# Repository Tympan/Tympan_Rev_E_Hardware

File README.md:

# Tympan Rev E Hardware Light
Repository for Tympan Rev E Light Electronics and case designs. This version of the Rev E is based on the Teensy 4.1 by PJRC and incorporates the Teensy 4.1 into our own design, as we did with the Tympan Rev D. This version is light in that it does not contain an on-board AIC, and is meant to be a PCB bridge between the Teensy 4.1 and the AIC Shield.

This is a work in progress.

## Check Back For Updates

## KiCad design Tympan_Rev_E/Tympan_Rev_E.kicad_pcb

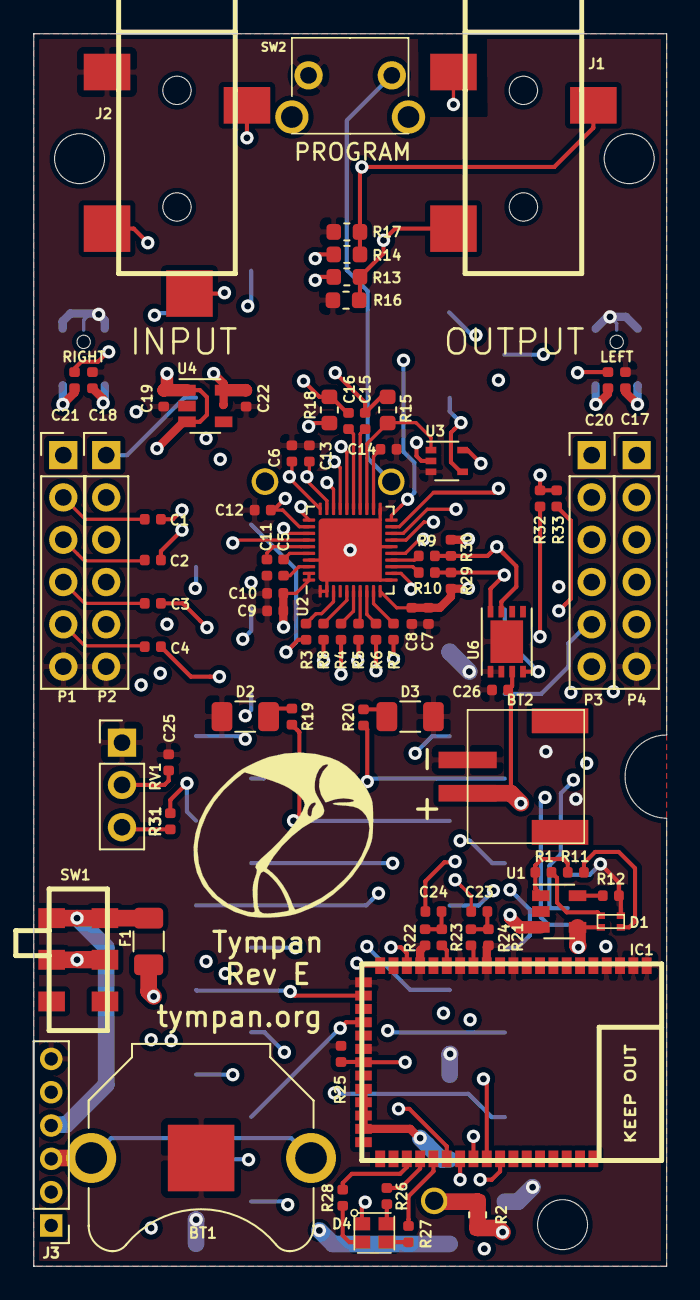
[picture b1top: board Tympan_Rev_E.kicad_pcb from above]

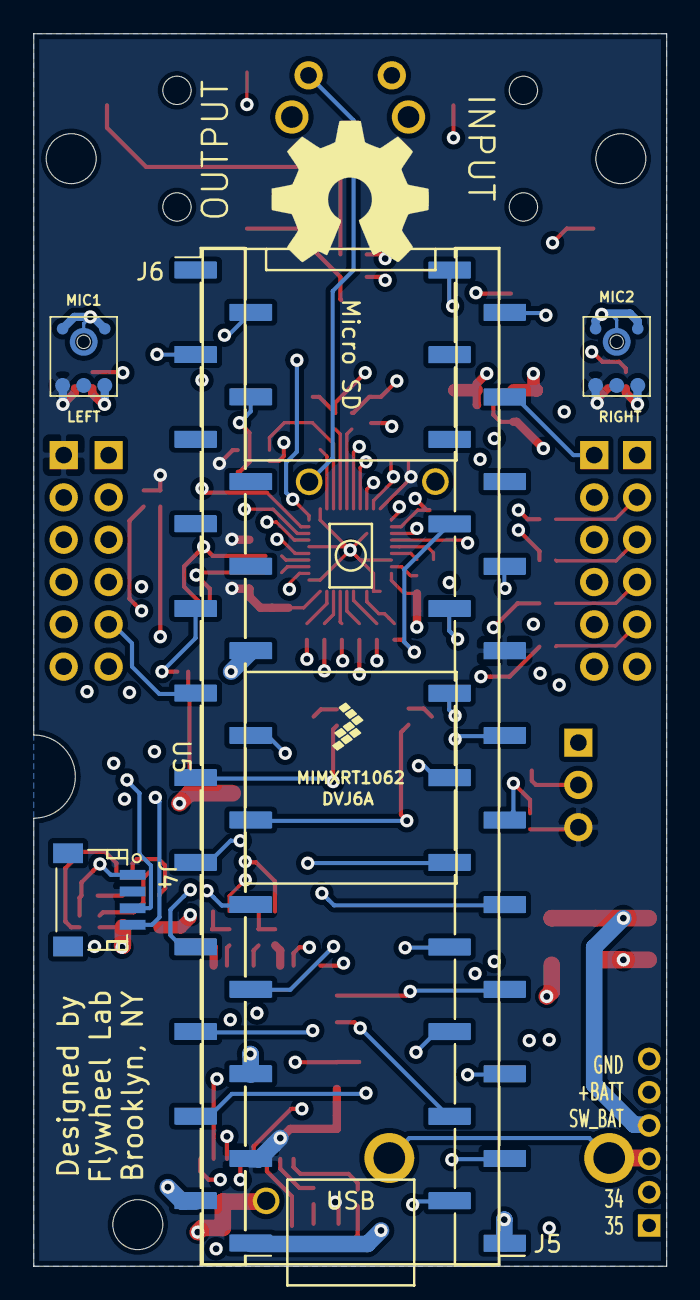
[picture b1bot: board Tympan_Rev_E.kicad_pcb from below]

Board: 4 copper layers, 38.0 x 74.0 mm, 91 parts (6 on the bottom side), 95 nets.

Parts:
BT1: Battery_Cell; BatteryHolder_Keystone_3001_1x12mm
BT2: 4UCON-20519; 4UCON-0217-20519
C1, C2, C3, C4, C5, C11, C15, C16, C23, C24: 2.2uF; C_0402_1005Metric
C6, C8, C10, C13, C17, C18, C25: 0.1uF; C_0402_1005Metric
C7, C9, C14: 10uF; C_0402_1005Metric
C12, C19, C20, C21, C22, C26: 1uF; C_0402_1005Metric
D1: APHB1608SGNC; ABHB1608S
D2, D3: LED; C_1206_3216Metric
D4: Led_RGB_CA; CLMVB-FKA-CFHEHLCBB7a363
F1: FUSE; C_1206_3216Metric
IC1: BC127
J1: SJ-3523-SMT-TR
J2: SJ-3524-SMT-TR-PI; SJ-3524-SMT-TR
J3: Conn_01x06; Pin_Header_Straight_1x06_Pitch2.00mm
J4: Qwiik Connector; JST_SH_SM04B-SRSS-TB_04x1.00mm_Angled
J5, J6: Conn_01x24; Pin_Header_Straight_1x24_Pitch2.54mm_SMD_Pin1Left
MIC1, MIC2: SPM0687LR5H-1
P1, P2, P3, P4: CONN_01X06; PinHeader_1x06_P2.54mm_Vertical
P6, P7, P8: CONN_01X01; MountingHole_3mm
R1, R11, R21, R22: 1K; R_0402_1005Metric
R2, R16, R17: DNP; R_0603_1608Metric
R3, R4, R5, R6, R7, R8, R9, R10: 33R; R_0402_1005Metric
R12: 2.2K; R_0402_1005Metric
R13, R14: 0R; R_0603_1608Metric
R15, R18: 2.2K; R_0603_1608Metric
R19, R20: 240R; R_0402_1005Metric
R23, R24, R31: 10K; R_0402_1005Metric
R25: 100K; R_0402_1005Metric
R26, R27, R28: 470R; R_0402_1005Metric
R29, R30, R32, R33: 4K7; R_0402_1005Metric
RV1: POT; PinHeader_1x03_P2.54mm_Vertical
SW1: CL-SB-22A
SW2: SW_Push; MJTP1117
U1: MCP73831; SOT-23-5
U2: TLV320AIC3206IRSBT; UQFN-40-1EP_5x5mm_P0.4mm_EP3.8x3.8mm
U3: 74LVC1G66; SOT-353_SC-70-5
U4: LP5907MFX-1.8; SOT-23-5
U5: Teensy4.1; Teensy41_SMT
U6: LC709203; WDFN8_3X4mm_0.65P

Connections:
+1V8: C9.1, C10.1, C12.1, C13.1, C22.1, P1.1, U2.29, U2.32, U2.39, U2.40, U4.5
+3V3: C6.2, C7.2, C8.2, C17.2, C18.2, D4.1, IC1.30, IC1.31, IC1.32, IC1.33, J4.2, J5.15, J6.22, MIC1.4, MIC2.4, P4.1, R29.1, R30.1, R31.2, R32.2, R33.2, RV1.3, U2.10, U2.30, U3.5, U5.15, U5.46
+BATT: BT2.1, C26.1, J3.5, SW1.2, SW1.5, U1.3, U6.3
/34_RX8: J3.2, U5.26
/35_TX8: J3.1, U5.27
/ALARMB: U5.33, U6.4
/BCLK: P2.3, R4.1, U5.43
/BT_CTS: IC1.40, U5.5
/BT_PIO0: IC1.23, U5.7
/BT_PIO5: IC1.25, U5.4
/BT_RTS: IC1.43, U5.6
/BT_RX: IC1.42, U5.3
/BT_TX: IC1.41, U5.2
/BT_nRESET: IC1.44, R31.1, U5.11
/DIN: R6.1, U5.9
/DIN_1: P4.3, U5.24
/DOUT: R7.1, U5.10
/DOUT_1: P4.2, U5.8
/HPL: R13.1, U2.31
/HPR: R14.1, U2.33
/IN1_L: C2.1, C23.1, U2.17
/IN1_R: C1.1, C24.1, U2.18
/IN2_L: C20.1, U2.19
/IN2_R: C21.1, U2.20
/L: J1.2, R13.2, R16.1
/LED_0: IC1.37, R28.1
/LED_1: IC1.38, R26.1
/LED_2: IC1.39, R27.1
/LED_A: R20.1, U5.37
/LED_R: R19.1, U5.38
/LOL: C3.1, IC1.21, U2.26
/LOR: C4.1, IC1.19, U2.27
/MCLK: P2.2, R8.1, U5.45
/MICBIAS: R15.1, U2.23, U3.1
/MICDET: J2.4, U2.34
/MISO: P3.3, U5.14
/MOSI: P3.4, U5.13
/M_BIAS: U3.4, U5.28
/M_BIAS_1: P2.1, U5.21
/PDM_CLK: P3.1, U2.15
/PDM_DAT: P3.2, U2.12
/POT: C25.1, RV1.2, U5.39
/PROGRAM: SW2.1, U5.53
/R: J1.3, R14.2, R17.1
/SCK: P3.5, U5.35
/SCL: R10.1, R29.2, U5.41, U6.8
/SCL2: J4.4, P4.5, R32.1, U5.16
/SDA: R9.1, R30.2, U5.40, U6.7
/SDA2: J4.3, P4.4, R33.1, U5.17
/SS: P3.6, U5.12
/SW_BATT: F1.2, J3.4, SW1.1, SW1.4
/VIN: C19.1, F1.1, U4.1, U4.3, U5.48
/VREGEN: IC1.28, R25.1, U5.36
/V_BAT: BT1.1, J3.3, U5.50
/V_USB: D1.3, R2.1, R2.2, U1.4, U5.49
/WCLK: P2.4, R5.1, U5.42
/nRESET: R3.1, U5.18
/nRESET_1: P2.5, U5.23
GND: BT1.2, BT2.2, C6.1, C7.1, C8.1, C9.2, C10.2, C11.2, C12.2, C13.2, C14.2, C17.1, C18.1, C19.2, C22.2, C25.2, C26.2, D1.2, D2.1, D3.1, IC1.1, IC1.2, IC1.3, IC1.4, IC1.11, IC1.13, IC1.15, IC1.18, IC1.20, IC1.22, IC1.27, J1.1, J2.1, J3.6, J4.1, MIC1.2, MIC1.3, MIC2.2, MIC2.3, P1.6, P2.6, P4.6, R12.2, R16.2, R17.2, R21.2, R22.2, R25.2, RV1.1, SW2.2, U1.2, U2.1, U2.2, U2.11, U2.16, U2.21, U2.28, U2.37, U2.41, U3.3, U4.2, U5.1, U5.34, U5.44, U5.47, U6.1, U6.2, U6.9
unnamed: C1.2, P1.2
unnamed: C2.2, P1.3
unnamed: C3.2, P1.4
unnamed: C4.2, P1.5
unnamed: C5.1, U2.36
unnamed: C5.2, U2.38
unnamed: C11.1, U2.35
unnamed: C14.1, U2.22
unnamed: C15.1, U2.24
unnamed: C15.2, J2.2, R15.2
unnamed: C16.1, U2.25
unnamed: C16.2, J2.3, R18.1
unnamed: C20.2, MIC1.1
unnamed: C21.2, MIC2.1
unnamed: C23.2, R21.1, R23.2
unnamed: C24.2, R22.1, R24.2
unnamed: D1.1, R1.1
unnamed: D1.4, R11.1
unnamed: D2.2, R19.2
unnamed: D3.2, R20.2
unnamed: D4.2, R26.2
unnamed: D4.3, R27.2
unnamed: D4.4, R28.2
unnamed: IC1.14, R23.1
unnamed: IC1.16, R24.1
unnamed: R1.2, R11.2, U1.1
unnamed: R3.2, U2.3
unnamed: R4.2, U2.6
unnamed: R5.2, U2.7
unnamed: R6.2, U2.8
unnamed: R7.2, U2.9
unnamed: R8.2, U2.5
unnamed: R9.2, U2.14
unnamed: R10.2, U2.13
unnamed: R12.1, U1.5
unnamed: R18.2, U3.2

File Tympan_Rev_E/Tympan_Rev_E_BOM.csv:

Reference, Quantity, Value, Footprint, Datasheet, Description, Manufacturer_Name, Manufacturer_Part_Number, Supplier_Name
BT1 ,1,Battery_Cell,Battery:BatteryHolder_Keystone_3001_1x12mm,~,,,,
BT2 ,1,4UCON-20519,Solutions:4UCON-0217-20519,,,,,
C14 C7 C9 ,3,10uF,Capacitor_SMD:C_0402_1005Metric,,,,,
C15 C16 C11 C5 C1 C2 C3 C4 C23 C24 ,10,2.2uF,Capacitor_SMD:C_0402_1005Metric,,,,,
C19 C22 C12 C20 C21 C26 ,6,1uF,Capacitor_SMD:C_0402_1005Metric,,,,,
C8 C10 C13 C6 C18 C17 C25 ,7,0.1uF,Capacitor_SMD:C_0402_1005Metric,,,,,
D1 ,1,APHB1608SGNC,Tympan:ABHB1608S,,,,,
D2 D3 ,2,LED,Capacitor_SMD:C_1206_3216Metric,,,,,
D4 ,1,Led_RGB_CA,Solutions:CLMVB-FKA-CFHEHLCBB7a363,,,,,
F1 ,1,FUSE,Capacitor_SMD:C_1206_3216Metric,,,,,
IC1 ,1,BC127,Tympan:BC127,https://www.bluecreation.com/fdownload.php?file=bc127-datash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,"Bluetooth Certified 4.0 Audio module (11.8mm x 18mm x 3.2mm), 51 pin, surface mounted",Blue Creation,bc127,RS
J1 ,1,SJ-3523-SMT-TR,Tympan:SJ-3523-SMT-TR,,,,,
J2 ,1,SJ-3524-SMT-TR-PI,Tympan:SJ-3524-SMT-TR,,,,,
J3 ,1,Conn_01x03,Connector_PinHeader_2.54mm:PinHeader_1x03_P2.54mm_Vertical,~,,,,
MIC1 MIC2 ,2,SPM0687LR5H-1,Tympan:SPM0687LR5H-1,,,,,
P4 P2 P1 P3 ,4,CONN_01X06,Connector_PinHeader_2.54mm:PinHeader_1x06_P2.54mm_Vertical,,,,,
P6 P7 P8 ,3,CONN_01X01,MountingHole:MountingHole_3mm,,,,,
R11 R1 R21 R22 ,4,1K,Resistor_SMD:R_0402_1005Metric,,,,,
R12 ,1,2.2K,Resistor_SMD:R_0402_1005Metric,,,,,
R13 R14 ,2,0R,Resistor_SMD:R_0603_1608Metric,,,,,
R15 R18 ,2,2.2K,Resistor_SMD:R_0603_1608Metric,,,,,
R16 R17 R2 ,3,DNP,Resistor_SMD:R_0603_1608Metric,,,,,
R19 R20 ,2,240R,Resistor_SMD:R_0402_1005Metric,,,,,
R23 R24 R31 ,3,10K,Resistor_SMD:R_0402_1005Metric,,,,,
R25 ,1,100K,Resistor_SMD:R_0402_1005Metric,,,,,
R26 R27 R28 ,3,470R,Resistor_SMD:R_0402_1005Metric,,,,,
R29 R30 R32 R33 ,4,4K7,Resistor_SMD:R_0402_1005Metric,,,,,
R3 R4 R5 R6 R7 R8 R9 R10 ,8,33R,Resistor_SMD:R_0402_1005Metric,,,,,
RV1 ,1,POT,Connector_PinHeader_2.54mm:PinHeader_1x03_P2.54mm_Vertical,,,,,
SW1 ,1,CL-SB-22A,Tympan:CL-SB-22A,,,,,
U1 ,1,MCP73831,Package_TO_SOT_SMD:SOT-23-5,,,,,
U2 ,1,TLV320AIC3206IRSBT,Package_DFN_QFN:UQFN-40-1EP_5x5mm_P0.4mm_EP3.8x3.8mm,,,,,
U3 ,1,74LVC1G66,Package_TO_SOT_SMD:SOT-353_SC-70-5,,,,,
U4 ,1,LP5907MFX-1.8,Package_TO_SOT_SMD:SOT-23-5,,,,,
U5 ,1,Teensy4.1,teensy:Teensy41_SMT,,,,,
U6 ,1,LC709203,Tympan:WDFN8_3X4mm_0.65P,,,,,

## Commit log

2020-01-31 Initial commit of schematics
    Basic copy paste of Tympan Rev D peripherals and power supply
    Needs Teensy 4 pin assignments
2020-02-01 First Draft Schematics for Rev E
2020-02-01 updated with some notes on schem
2020-02-03 Added notes
2020-08-03 Teensy 4.1
    Removed SD card
    I2C connections per Chip's recommendation
2020-08-21 Starting board layout
2020-08-22 draft layout of parts
2020-08-26 Component layout ready for routing
2020-09-02 Tracks Layout and Zone Fill
    Passing DRC with minor courtyard flags. Needs touchup of tracks and silk.
2020-09-03 updated silk
    tidied up tracks and updated silk. Moved fuse from bottom to top, now only parts on bottom are teensy and microphones.
2020-09-08 Added pullup on BT reset pin and rout for battery cable
2020-09-29 Re routing and adding gas guage
    added gas guage and routed fuse per design rec in issue #6
    added pullups to the I2C2 lines
    cleaned silk and copper pours
2020-09-29 Added header for headphone connections
2020-10-05 UPDATED SCHEMATICS PDF
2020-10-05 tweaked the copper pours
2021-01-23 Added csv BOM and swapped PDM nets
2021-02-05 updating readme
2021-04-26 Update to readme
2021-04-26 update to readme. Ready to start design changes
2021-04-26 Removed excess stuff
2021-04-27 ADDED TEENSY 41 PINS TO MIMX SYMBOL
    Checked and double checked pin associations
2021-05-03 Pinout Teensy and AIC symbol
2021-05-04 fit things into the title block
2021-05-04 EDIT
2021-05-04 added schematic pdf
2021-05-13 Made changes in Project.
    Check ReadMe for details on changes.
2021-05-13 added PDF of schematics
2021-05-15 fixes to silk and delete unused tracks
2021-05-15 added a link to the Circuit Hub project
2021-05-17 moved ICP Shield header
2021-05-17 updated PDF
2021-05-18 added 2 more breakouts
2021-05-18 update schematic pdf
2021-05-21 Added through hole prog button and Qwiic connector
2021-05-21 Verified Qwiic pin order
2021-05-24 Final Review
    Adjust silk and some internal traces.
    add net names to SMT headers for DFM and placement
    publish up to date PDF
2021-05-24 Updated Silk
    added version and note next to Quiic/Stemma connector
2021-06-21 Enclosure CAD for Test Print
2021-06-23 Updated Rev-E2 Enclosure
2021-06-23 Corrected LED port alignment
2021-06-23 Added belt clip holes and revised lettering
2021-06-24 Updated Enclosure
    Adjusted heat set insert hole for belt clip
    Added space for label
2021-06-28 updates to the enclosure files
    I'm adding the mods that I made to the enclosure
2021-08-06 Added Case STL Enclosure File
2021-08-06 Added enclosure STLs
    Production STL files uploaded
2022-01-25 Case Export
2022-01-26 New BLE module and small fixes
    added bc127-ext
    moved fuse on input
    added antenna
    added pi type matching circuit
    repositioned radio module
    cleaned up tracks
2022-01-26 Updated read me
2022-02-16 Working out supply chain kinks and polishing this version
2022-02-16 Freezing. In Production
    Project is on Circuit Hub in Revision 8
    https://circuithub.com/projects/biomurph/Tympan_Rev_E/revisions/40091/viewer
2022-02-17 Production Update
    Change U6 footprint to match package
2022-06-04 Added initial Blender model
2022-06-06 change in folder hierarchy
2022-06-11 Fixed labelling, Re-rendered images for PR resubmission
2022-06-23 update U6 footprint
2023-12-04 Files cleanup
    Removed older versions of the kicad files from previous kicad releases.
2023-12-04 Upate Readme
    Initial commit of this folder to reduce the design of the Tympan Rev E to only incorporate the AIC Shield.
    The idea here is to make a low-cost Tympan that can go along with the AIC Shields still in stock.
2024-01-17 Swapped out the BLE module
    Replace the BC127 with the MDBT50Q-1MV2 nRF52840 module
    The new module will be targeted as an Adafriut nRF52840 Feather Express
    Made basic functional connections
2024-01-19 Revert "Swapped out the BLE module"
    This reverts commit 95fca984de24e2c498e4892b05c2135819655856.
